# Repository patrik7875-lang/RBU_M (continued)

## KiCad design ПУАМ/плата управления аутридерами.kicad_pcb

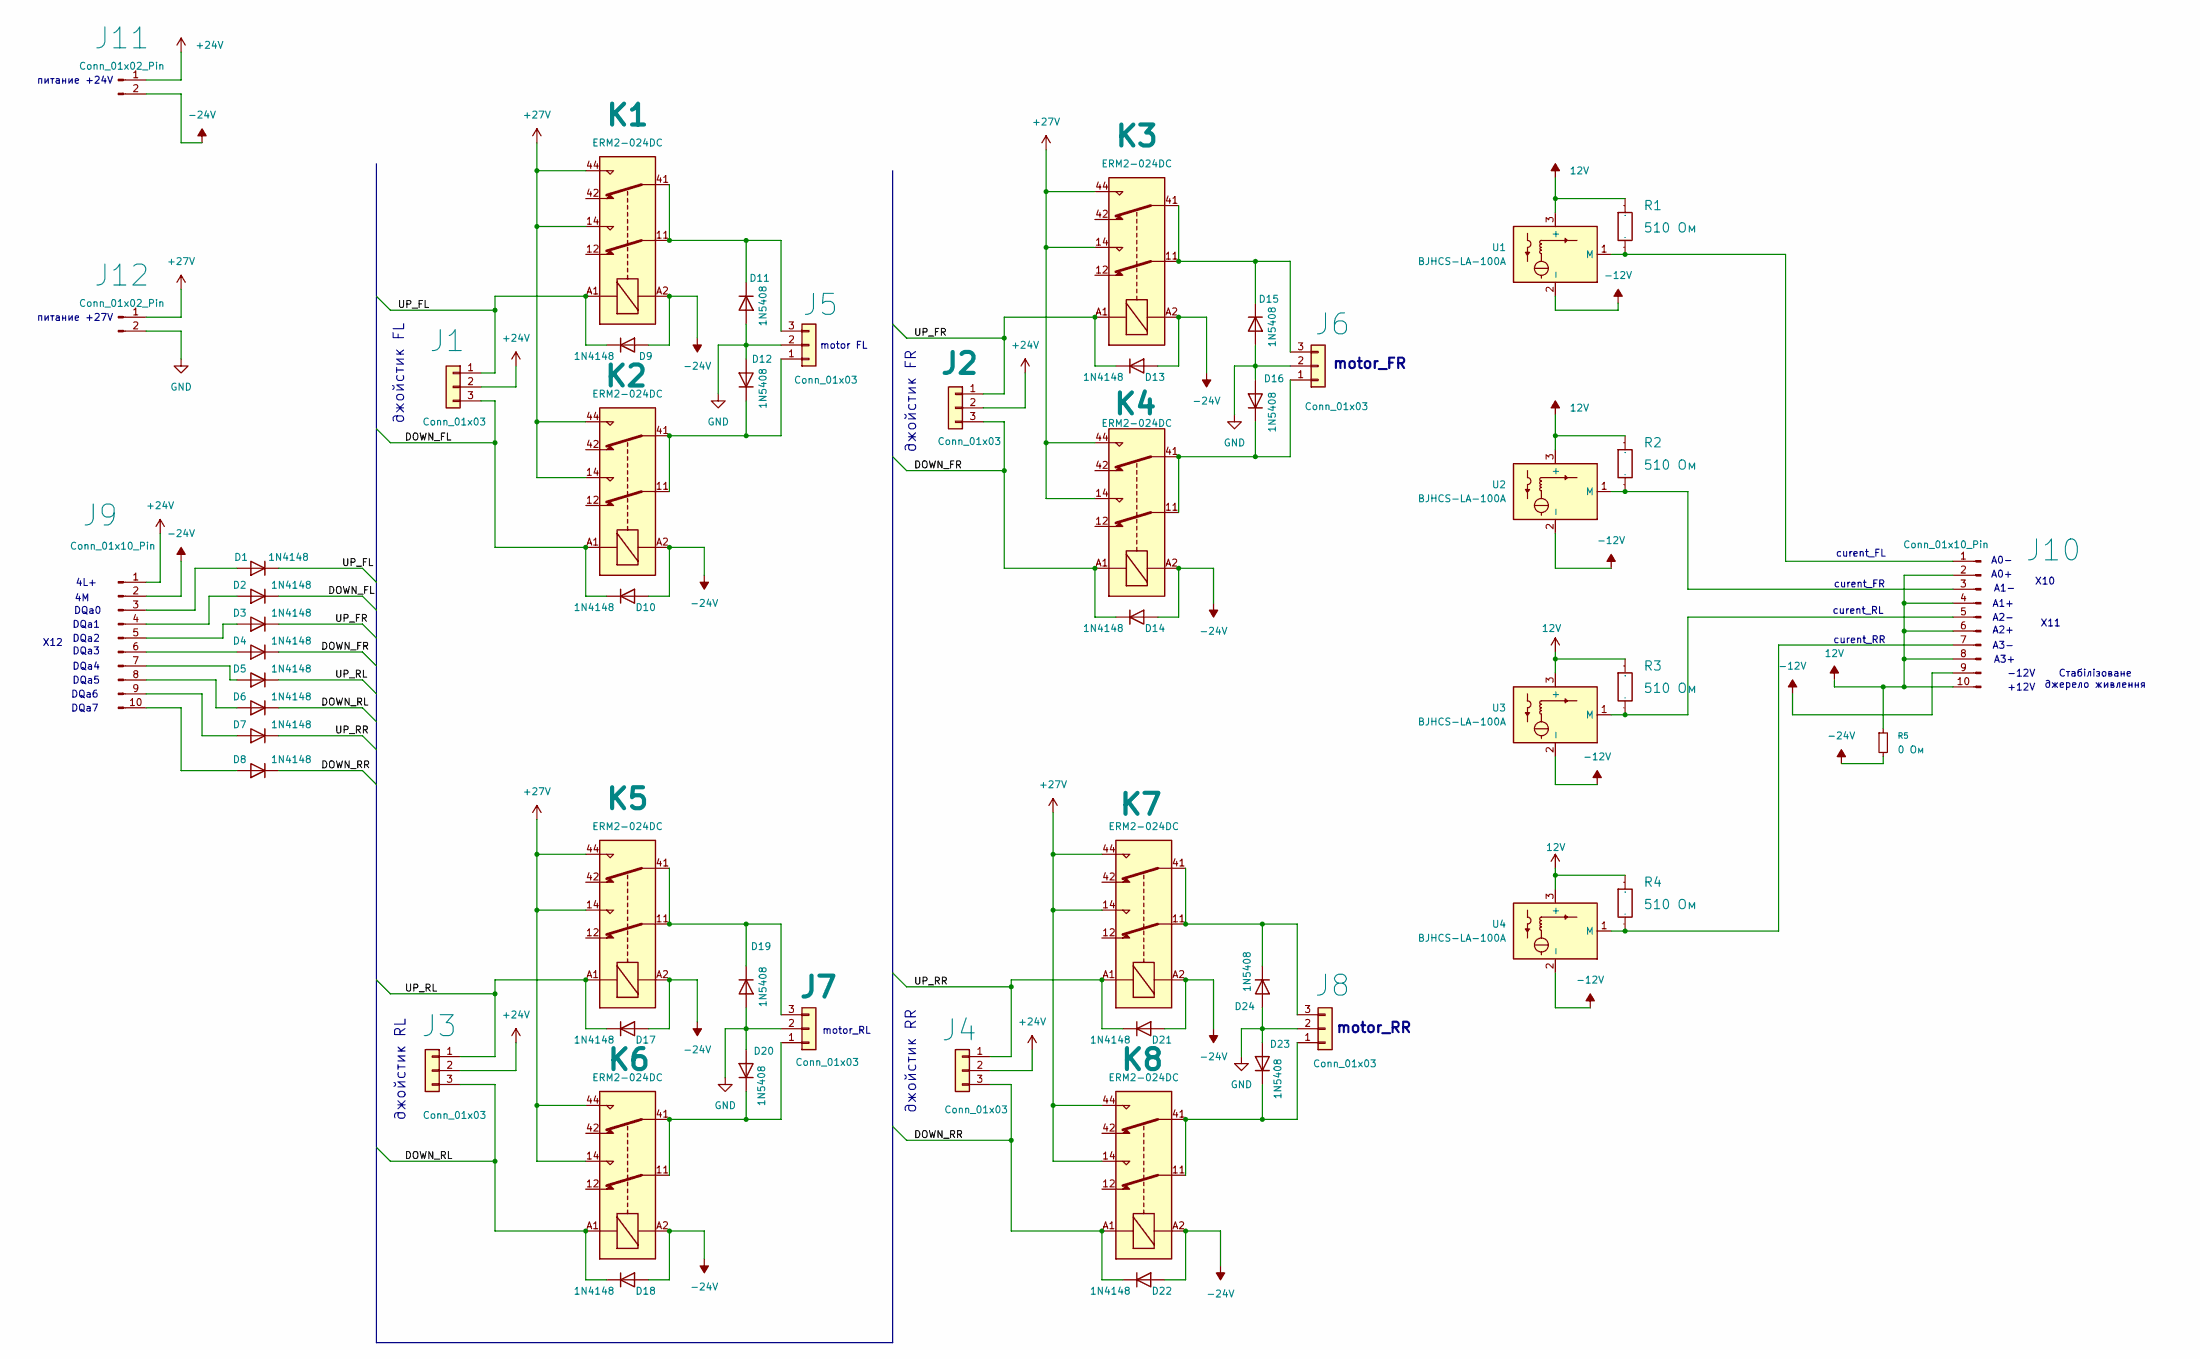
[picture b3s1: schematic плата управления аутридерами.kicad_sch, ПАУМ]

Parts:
D1, D2, D3, D4, D5, D6, D7, D8, D9, D10, D13, D14, D17, D18, D21, D22: 1N4148; D_SOD-123
D11, D12, D15, D16, D19, D20, D23, D24: 1N5408; D_DO-201AD_P15.24mm_Horizontal
J1, J2, J3, J4, J5, J6, J7, J8: Conn_01x03; Molex_KK-254_AE-6410-03A_1x03_P2.54mm_Vertical
J9: Conn_01x10_Pin; TerminalBlock_Phoenix_PT-1,5-10-5.0-H_1x10_P5.00mm_Horizont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
J10: Conn_01x10_Pin; Molex_KK-254_AE-6410-10A_1x10_P2.54mm_Vertical
J11, J12: Conn_01x02_Pin; TerminalBlock_Phoenix_PT-1,5-2-5.0-H_1x02_P5.00mm_Horizontal
K1, K2, K3, K4, K5, K6, K7, K8: ERM2-024DC
R1, R2, R3, R4: 510 Ом; R_Axial_DIN0411_L9.9mm_D3.6mm_P12.70mm_Horizontal; Manufacturer Part SC0805J1000F4ANRH
R5: 0 Ом; R_1206_3216Metric
U1, U2, U3, U4: BJHCS-LA-100A

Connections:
12V: J10.2, J10.4, J10.6, J10.8, J10.10, R1.1, R2.1, R3.1, R4.1, R5.1, U1.3 (+), U2.3 (+), U3.3 (+), U4.3 (+)
+24V: J1.2, J2.2, J3.2, J4.2, J9.1, J11.1
+27V: J12.1, K1.14, K1.44, K2.14, K2.44, K3.14, K3.44, K4.14, K4.44, K5.14, K5.44, K6.14, K6.44, K7.14, K7.44, K8.14, K8.44
-12V: J10.9, U1.2 (-), U2.2 (-), U3.2 (-), U4.2 (-)
-24V: D9.2 (A), D10.2 (A), D13.2 (A), D14.2 (A), D17.2 (A), D18.2 (A), D21.2 (A), D22.2 (A), J9.2, J11.2, K1.A2, K2.A2, K3.A2, K4.A2, K5.A2, K6.A2, K7.A2, K8.A2, R5.2
/DOWN_FL: D2.1 (K), D10.1 (K), J1.3, K2.A1
/DOWN_FR: D4.1 (K), D14.1 (K), J2.3, K4.A1
/DOWN_RL: D6.1 (K), D18.1 (K), J3.3, K6.A1
/DOWN_RR: D8.1 (K), D22.1 (K), J4.3, K8.A1
/UP_FL: D1.1 (K), D9.1 (K), J1.1, K1.A1
/UP_FR: D3.1 (K), D13.1 (K), J2.1, K3.A1
/UP_RL: D5.1 (K), D17.1 (K), J3.1, K5.A1
/UP_RR: D7.1 (K), D21.1 (K), J4.1, K7.A1
GND: D11.2 (A), D12.2 (A), D15.2 (A), D16.2 (A), D19.2 (A), D20.2 (A), D23.2 (A), D24.2 (A), J5.2, J6.2, J7.2, J8.2, J12.2
unnamed: D1.2 (A), J9.3
unnamed: D2.2 (A), J9.4
unnamed: D3.2 (A), J9.5
unnamed: D4.2 (A), J9.6
unnamed: D5.2 (A), J9.7
unnamed: D6.2 (A), J9.8
unnamed: D7.2 (A), J9.9
unnamed: D8.2 (A), J9.10
unnamed: D11.1 (K), J5.3, K1.11, K1.41
unnamed: D12.1 (K), J5.1, K2.11, K2.41
unnamed: D15.1 (K), J6.3, K3.11, K3.41
unnamed: D16.1 (K), J6.1, K4.11, K4.41
unnamed: D19.1 (K), J7.3, K5.11, K5.41
unnamed: D20.1 (K), J7.1, K6.11, K6.41
unnamed: D23.1 (K), J8.1, K8.11, K8.41
unnamed: D24.1 (K), J8.3, K7.11, K7.41
unnamed: J10.1, R1.2, U1.1 (M)
unnamed: J10.3, R2.2, U2.1 (M)
unnamed: J10.5, R3.2, U3.1 (M)
unnamed: J10.7, R4.2, U4.1 (M)

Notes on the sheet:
джойстик FL
DQa6
джойстик RL
DQa0
джойстик RR
curent_RR
DQa5
curent_FL
DQa4
-12V
A1-
DQa1
motor_FR
curent_RL
питание +27V
X11
motor_RR
DQa3
A3-
джойстик FR
DQa2
Стабілізоване джерело живлення
X12
4L+
motor FL
+12V
DQa7
motor_RL
A0+
A2-
A1+
A0-
X10
curent_FR
питание +24V
A3+
A2+

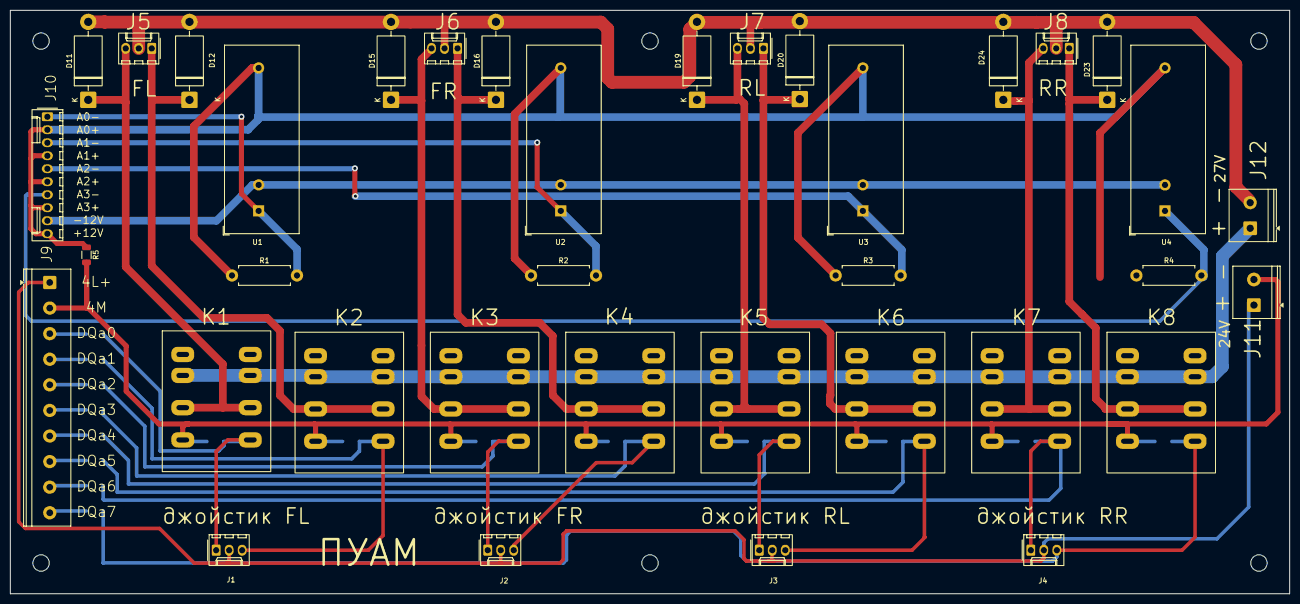
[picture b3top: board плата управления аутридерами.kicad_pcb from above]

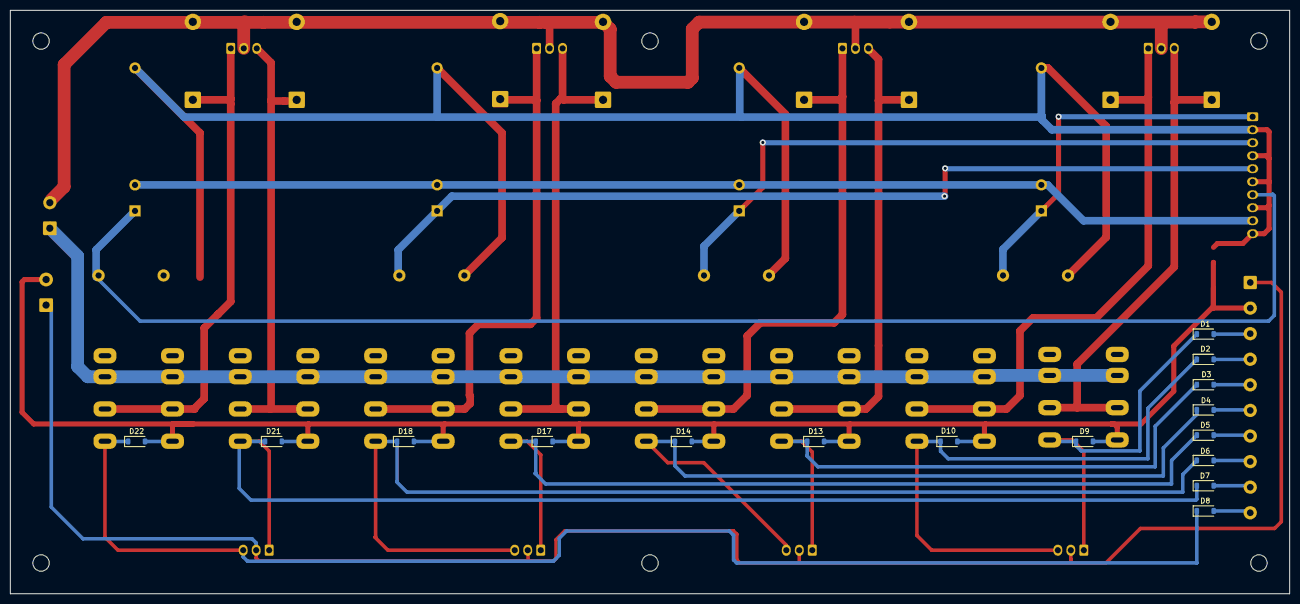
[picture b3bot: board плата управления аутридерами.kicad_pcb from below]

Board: 2 copper layers, 250.0 x 114.0 mm, 53 parts (16 on the bottom side), 34 nets.

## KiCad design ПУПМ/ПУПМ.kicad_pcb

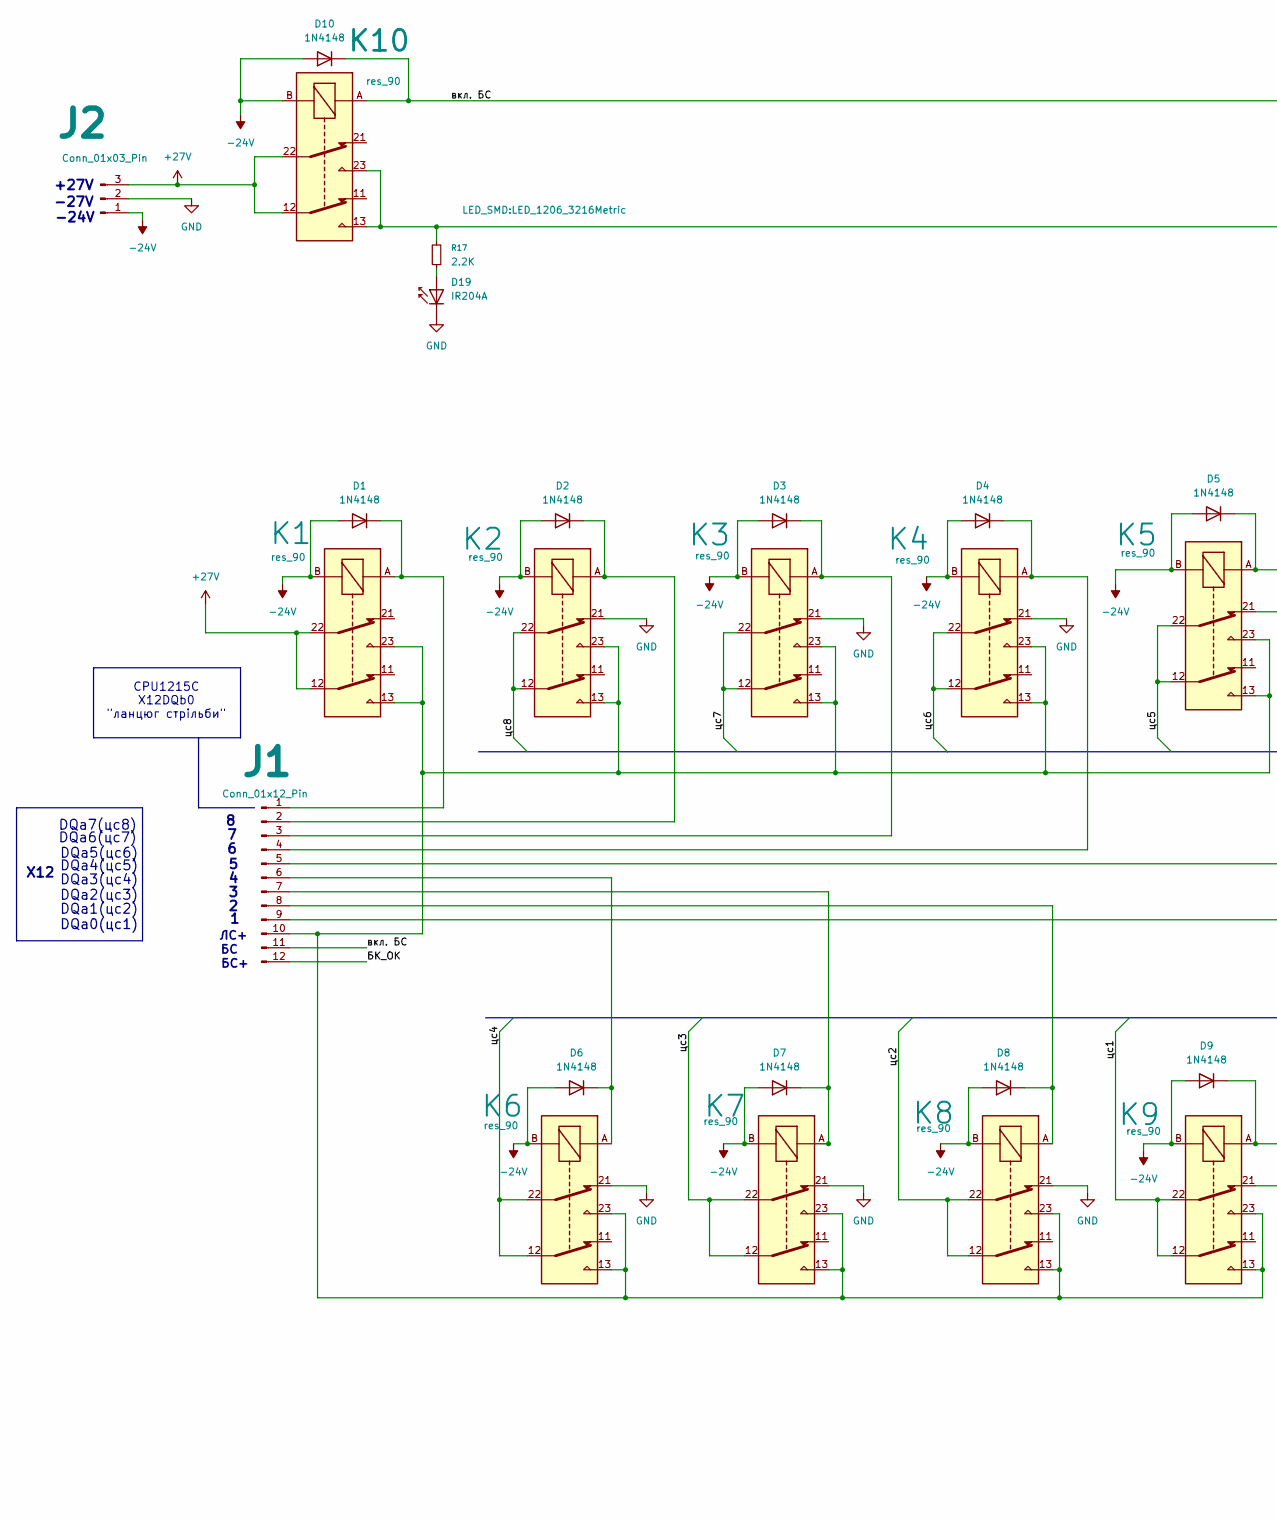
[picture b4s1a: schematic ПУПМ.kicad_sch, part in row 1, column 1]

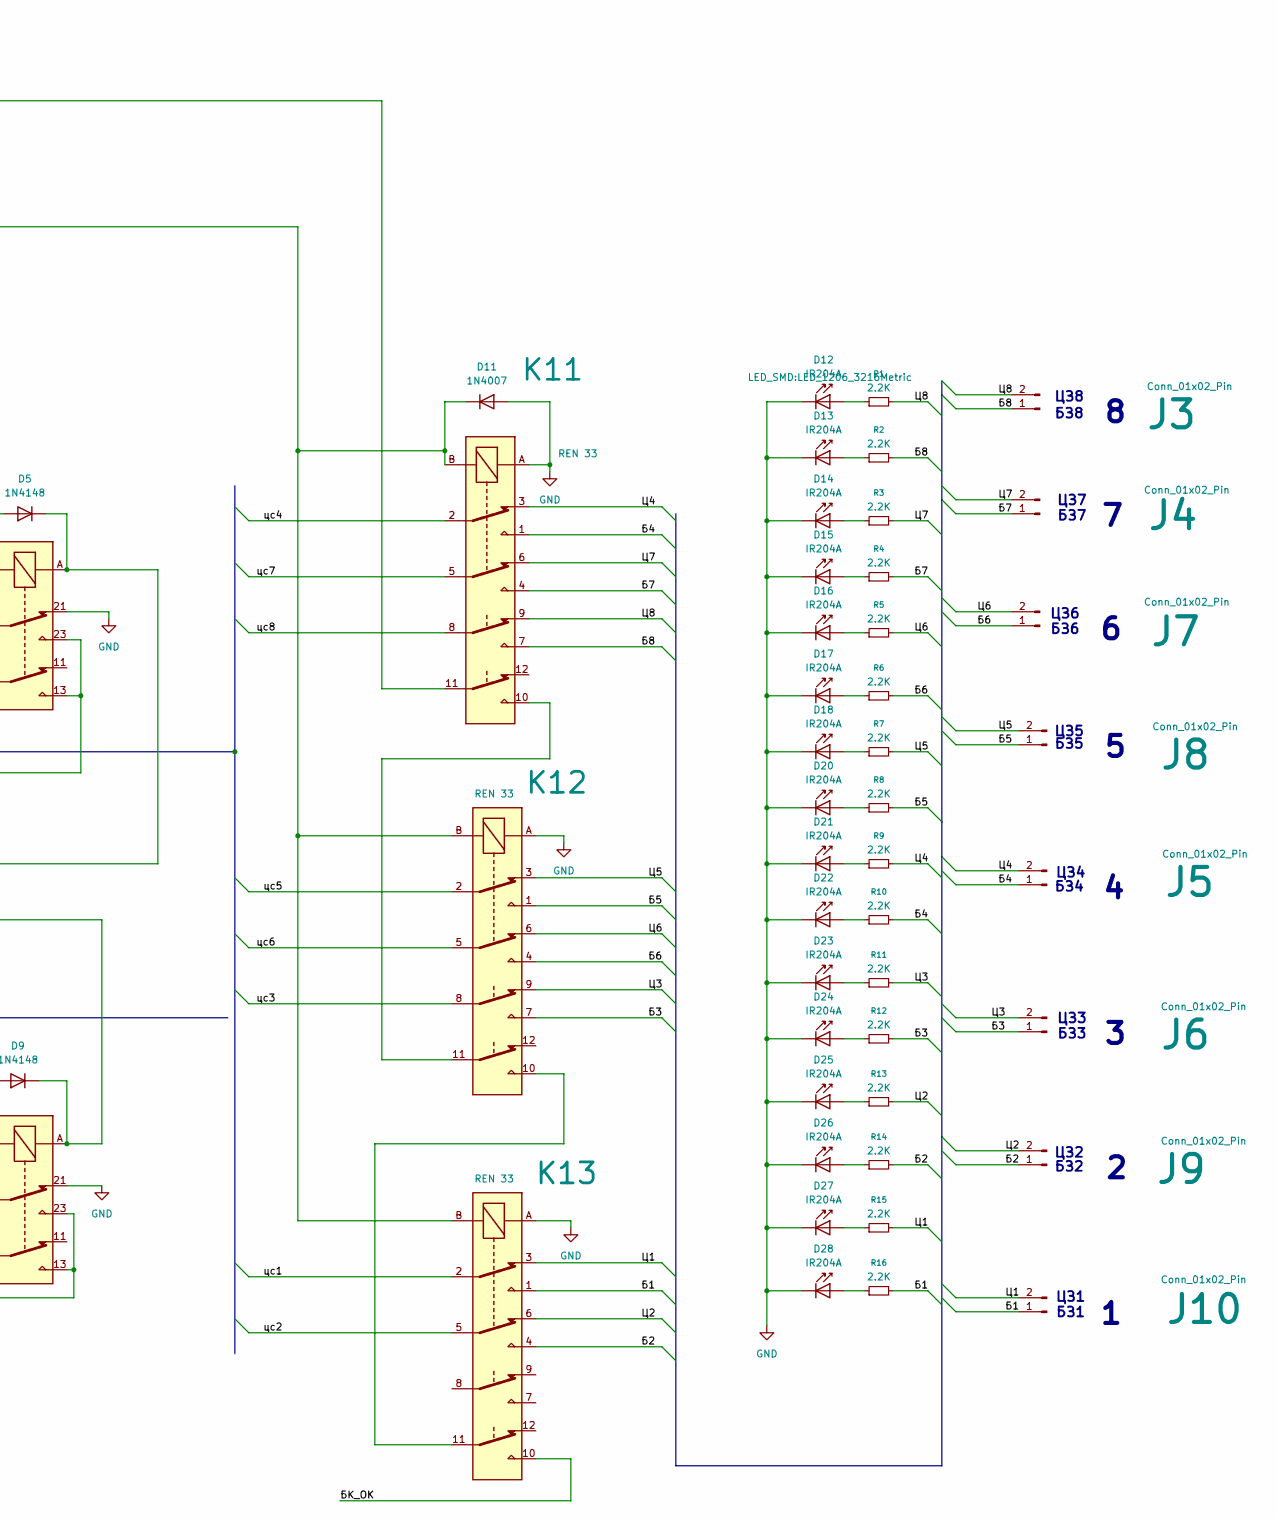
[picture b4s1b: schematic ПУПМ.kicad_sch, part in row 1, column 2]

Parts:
D1, D2, D3, D4, D5, D6, D7, D8, D9, D10: 1N4148; D_SOD-123
D11: 1N4007; D_DO-41_SOD81_P10.16mm_Horizontal
D12, D13, D14, D15, D16, D17, D18, D19, D20, D21, D22, D23, D24, D25, D26, D27, D28: IR204A; LED_1206_3216Metric
J1: Conn_01x12_Pin; TerminalBlock_Phoenix_PT-1,5-12-5.0-H_1x12_P5.00mm_Horizont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
J2: Conn_01x03_Pin; TerminalBlock_MetzConnect_Type701_RT11L03HGLU_1x03_P6.35mm_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
J3, J4, J5, J6, J7, J8, J9, J10: Conn_01x02_Pin; TerminalBlock_MetzConnect_Type701_RT11L02HGLU_1x02_P6.35mm_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
K1, K2, K3, K4, K5, K6, K7, K8, K9, K10: res_90; res90
K11, K12, K13: REN 33
R1, R2, R3, R4, R5, R6, R7, R8, R9, R10, R11, R12, R13, R14, R15, R16, R17: 2.2K; R_1206_3216Metric

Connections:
+27V: J2.3, K1.12, K1.22, K10.12, K10.22
-24V: D1.2 (A), D2.2 (A), D3.2 (A), D4.2 (A), D5.2 (A), D6.2 (A), D7.2 (A), D8.2 (A), D9.2 (A), D10.2 (A), J2.1, K1.B, K2.B, K3.B, K4.B, K5.B, K6.B, K7.B, K8.B, K9.B, K10.B
/Б1: J10.1, K13.1, R16.2
/Б2: J9.1, K13.4, R14.2
/Б3: J6.1, K12.7, R12.2
/Б4: J5.1, K11.1, R10.2
/Б5: J8.1, K12.1, R8.2
/Б6: J7.1, K12.4, R6.2
/Б7: J4.1, K11.4, R4.2
/Б8: J3.1, K11.7, R2.2
/БК_ОК: J1.12, K13.10
/Ц1: J10.2, K13.3, R15.2
/Ц2: J9.2, K13.6, R13.2
/Ц3: J6.2, K12.9, R11.2
/Ц4: J5.2, K11.3, R9.2
/Ц5: J8.2, K12.3, R7.2
/Ц6: J7.2, K12.6, R5.2
/Ц7: J4.2, K11.6, R3.2
/Ц8: J3.2, K11.9, R1.2
/вкл. БС: D10.1 (K), J1.11, K10.A, K11.11
/цс1: K9.12, K9.22, K13.2
/цс2: K8.12, K8.22, K13.5
/цс3: K7.12, K7.22, K12.8
/цс4: K6.12, K6.22, K11.2
/цс5: K5.12, K5.22, K12.2
/цс6: K4.12, K4.22, K12.5
/цс7: K3.12, K3.22, K11.5
/цс8: K2.12, K2.22, K11.8
GND: D11.2 (A), D12.1 (K), D13.1 (K), D14.1 (K), D15.1 (K), D16.1 (K), D17.1 (K), D18.1 (K), D19.1 (K), D20.1 (K), D21.1 (K), D22.1 (K), D23.1 (K), D24.1 (K), D25.1 (K), D26.1 (K), D27.1 (K), D28.1 (K), J2.2, K2.21, K3.21, K4.21, K5.21, K6.21, K7.21, K8.21, K9.21, K11.A, K12.A, K13.A
unnamed: D1.1 (K), J1.1, K1.A
unnamed: D2.1 (K), J1.2, K2.A
unnamed: D3.1 (K), J1.3, K3.A
unnamed: D4.1 (K), J1.4, K4.A
unnamed: D5.1 (K), J1.5, K5.A
unnamed: D6.1 (K), J1.6, K6.A
unnamed: D7.1 (K), J1.7, K7.A
unnamed: D8.1 (K), J1.8, K8.A
unnamed: D9.1 (K), J1.9, K9.A
unnamed: D11.1 (K), K10.13, K10.23, K11.B, K12.B, K13.B, R17.2
unnamed: D12.2 (A), R1.1
unnamed: D13.2 (A), R2.1
unnamed: D14.2 (A), R3.1
unnamed: D15.2 (A), R4.1
unnamed: D16.2 (A), R5.1
unnamed: D17.2 (A), R6.1
unnamed: D18.2 (A), R7.1
unnamed: D19.2 (A), R17.1
unnamed: D20.2 (A), R8.1
unnamed: D21.2 (A), R9.1
unnamed: D22.2 (A), R10.1
unnamed: D23.2 (A), R11.1
unnamed: D24.2 (A), R12.1
unnamed: D25.2 (A), R13.1
unnamed: D26.2 (A), R14.1
unnamed: D27.2 (A), R15.1
unnamed: D28.2 (A), R16.1
unnamed: J1.10, K1.13, K1.23, K2.13, K2.23, K3.13, K3.23, K4.13, K4.23, K5.13, K5.23, K6.13, K6.23, K7.13, K7.23, K8.13, K8.23, K9.13, K9.23
unnamed: K11.10, K12.11
unnamed: K12.10, K13.11

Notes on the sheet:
БЗ2
X12
ЦЗ7
DQa1(цс2)
ЦЗ5
БЗ5
ЦЗ1
ЦЗ2
ЛС+
ЦЗ8
DQa7(цс8)
ЦЗ4
DQa5(цс6)
DQa6(цс7)
БЗ3
DQa2(цс3)
DQa4(цс5)
БЗ1
DQa0(цс1)
ЦЗ6
-27V
-24V
БC+
CPU1215C X12DQb0 "ланцюг стрільби"
DQa3(цс4)
БЗ4
+27V
БЗ6
БЗ8
БЗ7
ЦЗ3

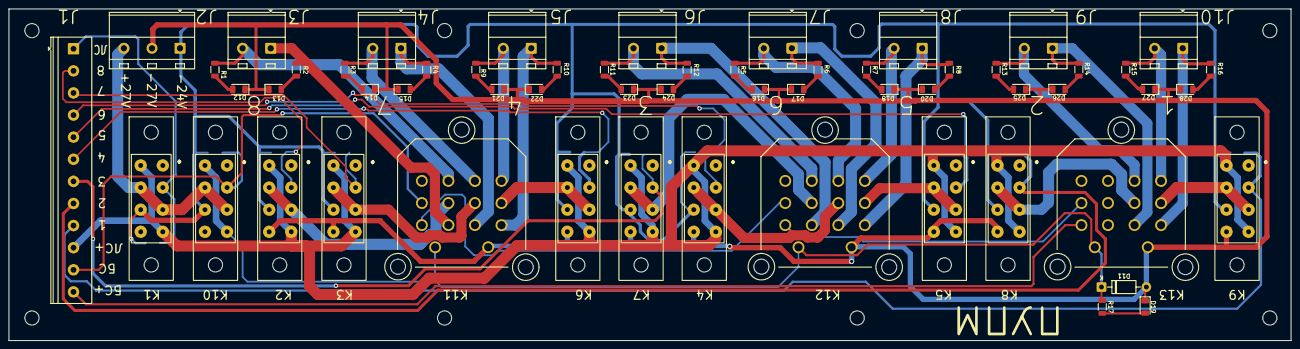
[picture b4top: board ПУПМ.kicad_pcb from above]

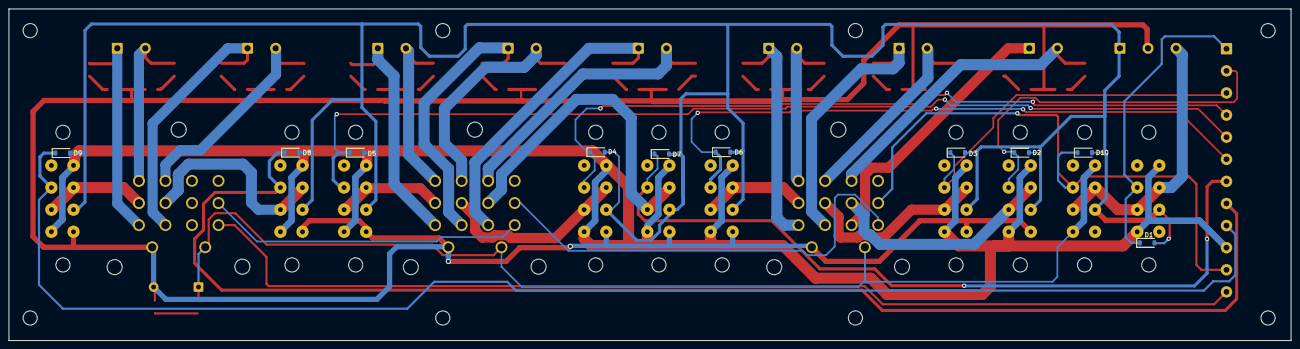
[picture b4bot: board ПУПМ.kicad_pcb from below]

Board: 2 copper layers, 290.0 x 75.0 mm, 68 parts (10 on the bottom side), 59 nets.
